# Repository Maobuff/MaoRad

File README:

#MadRad
## My(maobuff) attempt at catching gamma photons.

[Schemaic](doc/schematic.pdf)

##Device assembled

##Output waveform example

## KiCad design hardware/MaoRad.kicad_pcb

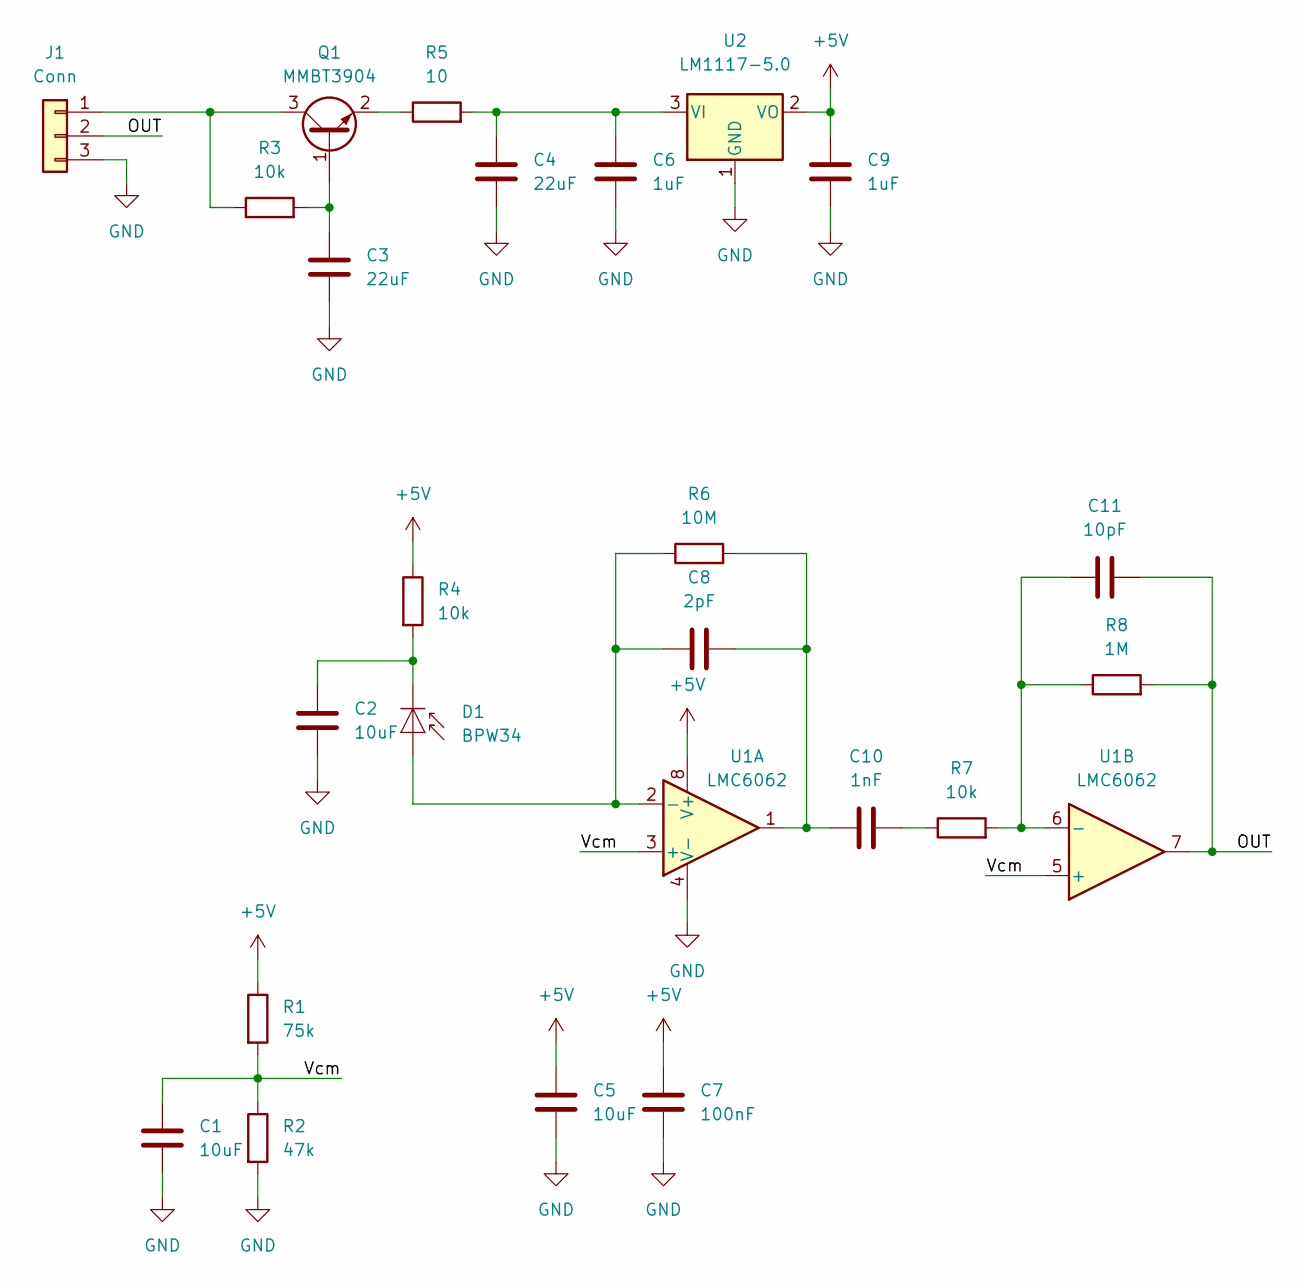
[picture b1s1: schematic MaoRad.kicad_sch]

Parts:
C1, C2, C5: 10uF; C_1206_3216Metric_Pad1.33x1.80mm_HandSolder
C3, C4: 22uF; C_1206_3216Metric_Pad1.33x1.80mm_HandSolder
C6, C9: 1uF; C_1206_3216Metric_Pad1.33x1.80mm_HandSolder
C7: 100nF; C_1206_3216Metric_Pad1.33x1.80mm_HandSolder
C8: 2pF; C_1206_3216Metric_Pad1.33x1.80mm_HandSolder
C10: 1nF; C_1206_3216Metric_Pad1.33x1.80mm_HandSolder
C11: 10pF; C_1206_3216Metric_Pad1.33x1.80mm_HandSolder
D1: BPW34; Osram_SMD-DIL2_4.5x4.0mm
J1: Conn; PinHeader_1x03_P2.54mm_Horizontal
Q1: MMBT3904; SOT-23
R1: 75k; R_1206_3216Metric_Pad1.30x1.75mm_HandSolder
R2: 47k; R_1206_3216Metric_Pad1.30x1.75mm_HandSolder
R3, R4, R7: 10k; R_1206_3216Metric_Pad1.30x1.75mm_HandSolder
R5: 10; R_1206_3216Metric_Pad1.30x1.75mm_HandSolder
R6: 10M; R_1206_3216Metric_Pad1.30x1.75mm_HandSolder
R8: 1M; R_1206_3216Metric_Pad1.30x1.75mm_HandSolder
U1: LMC6062
U2: LM1117-5.0; SOT-223-3_TabPin2

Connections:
+5V: C5.1, C7.1, C9.1, R1.1, R4.1, U1.8 (V+), U2.2 (VO)
/OUT: C11.2, J1.2, R8.2, U1.7
/Vcm: C1.1, R1.2, R2.1, U1.3 (+), U1.5 (+)
GND: C1.2, C2.2, C3.2, C4.2, C5.2, C6.2, C7.2, C9.2, J1.3, R2.2, U1.4 (V-), U2.1 (GND)
unnamed: C2.1, D1.1 (K), R4.2
unnamed: C3.1, Q1.1 (B), R3.2
unnamed: C4.1, C6.1, R5.2, U2.3 (VI)
unnamed: C8.1, D1.2 (A), R6.1, U1.2 (-)
unnamed: C8.2, C10.1, R6.2, U1.1
unnamed: C10.2, R7.1
unnamed: C11.1, R7.2, R8.1, U1.6 (-)
unnamed: J1.1, Q1.3 (C), R3.1
unnamed: Q1.2 (E), R5.1

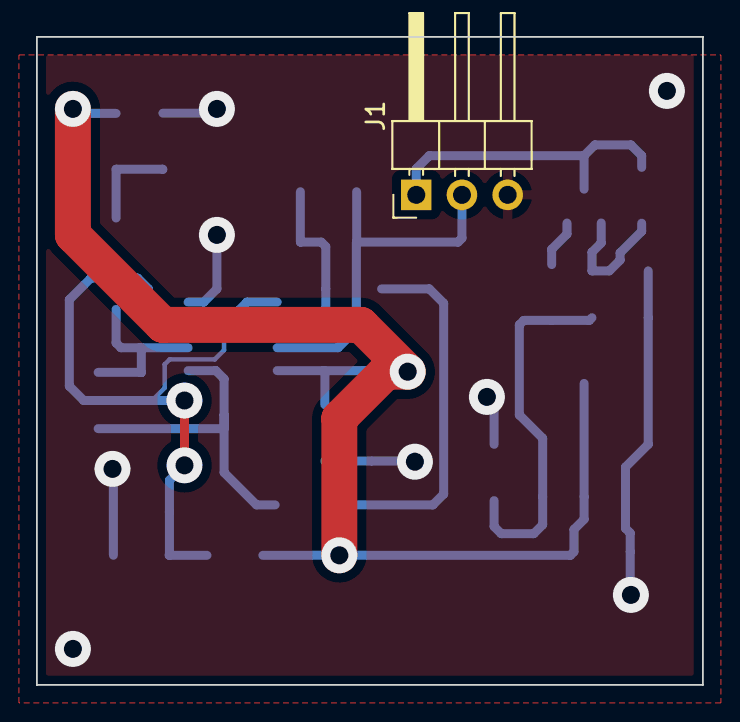
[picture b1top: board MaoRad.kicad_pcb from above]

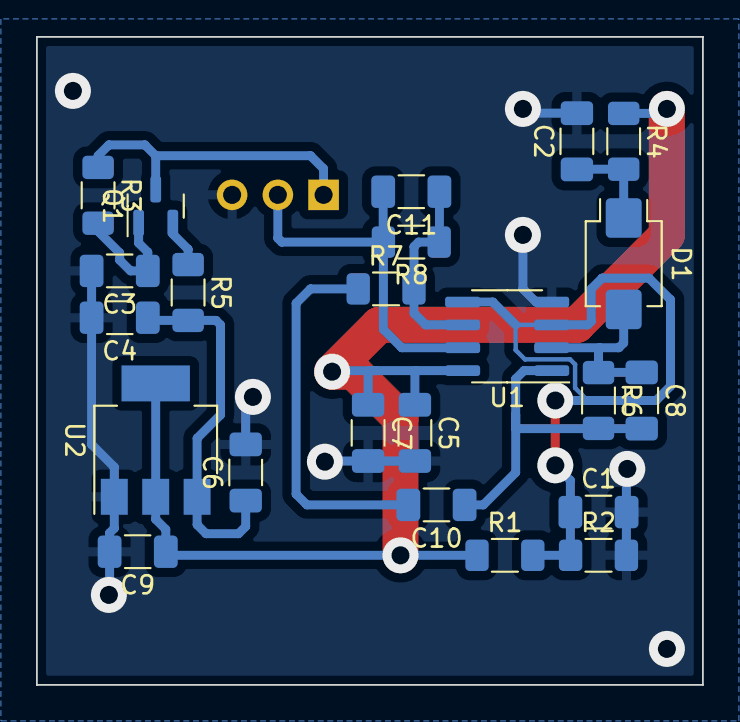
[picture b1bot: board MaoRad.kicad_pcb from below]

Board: 2 copper layers, 37.0 x 36.0 mm, 24 parts (23 on the bottom side), 13 nets.

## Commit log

2022-08-17 feat: init
2022-08-17 fix: formating
2022-08-17 fix: pictures
2022-08-17 fix: wrong image
2022-08-17 fix: improved README
2022-08-17 fix: lmc662
2022-08-18 fix: README.md
